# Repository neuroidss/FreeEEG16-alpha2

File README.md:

# FreeEEG16-alpha2

[https://neuroidss.github.io/NEURO-CULTIVATION/](https://neuroidss.github.io/NEURO-CULTIVATION/)

This project relies on a custom ultra-high-density EEG device, NOT a standard medical or consumer EEG headset.
- **Device Name:** FreeEEG16-alpha2
- **Form Factor:** 26mm diameter circular PCB.
- **Electrode Array:** 18 pogo pins tightly packed within the 26mm area.
  - 16 Active Positive Channels (+)
  - 1 Common Reference (-)
  - 1 Ground (GND)
- **Placement:** Works entirely locally, primarily targeted at the Pz (parietal) placement.
- **Key Capability:** NO distant electrodes are required. Reference and Ground are located in the same 26mm cluster as the active channels.
- **Performance:** When placed on Pz, the system provides a high-fidelity real-time loop. Users can observe immediate bio-reactive changes in procedural shaders, minimizing the cognitive load required to establish stable neurofeedback.

[Neuro_Test_Bench_PRO_16CH](https://neuroidss.github.io/FreeEEG16-alpha2/Neuro_Test_Bench/Neuro_Test_Bench_PRO_16CH.html)

[FreeEEG16-alpha_2_1_gerbers](https://github.com/neuroidss/FreeEEG16-alpha2/releases/tag/FreeEEG16-alpha_2_1_gerbers)

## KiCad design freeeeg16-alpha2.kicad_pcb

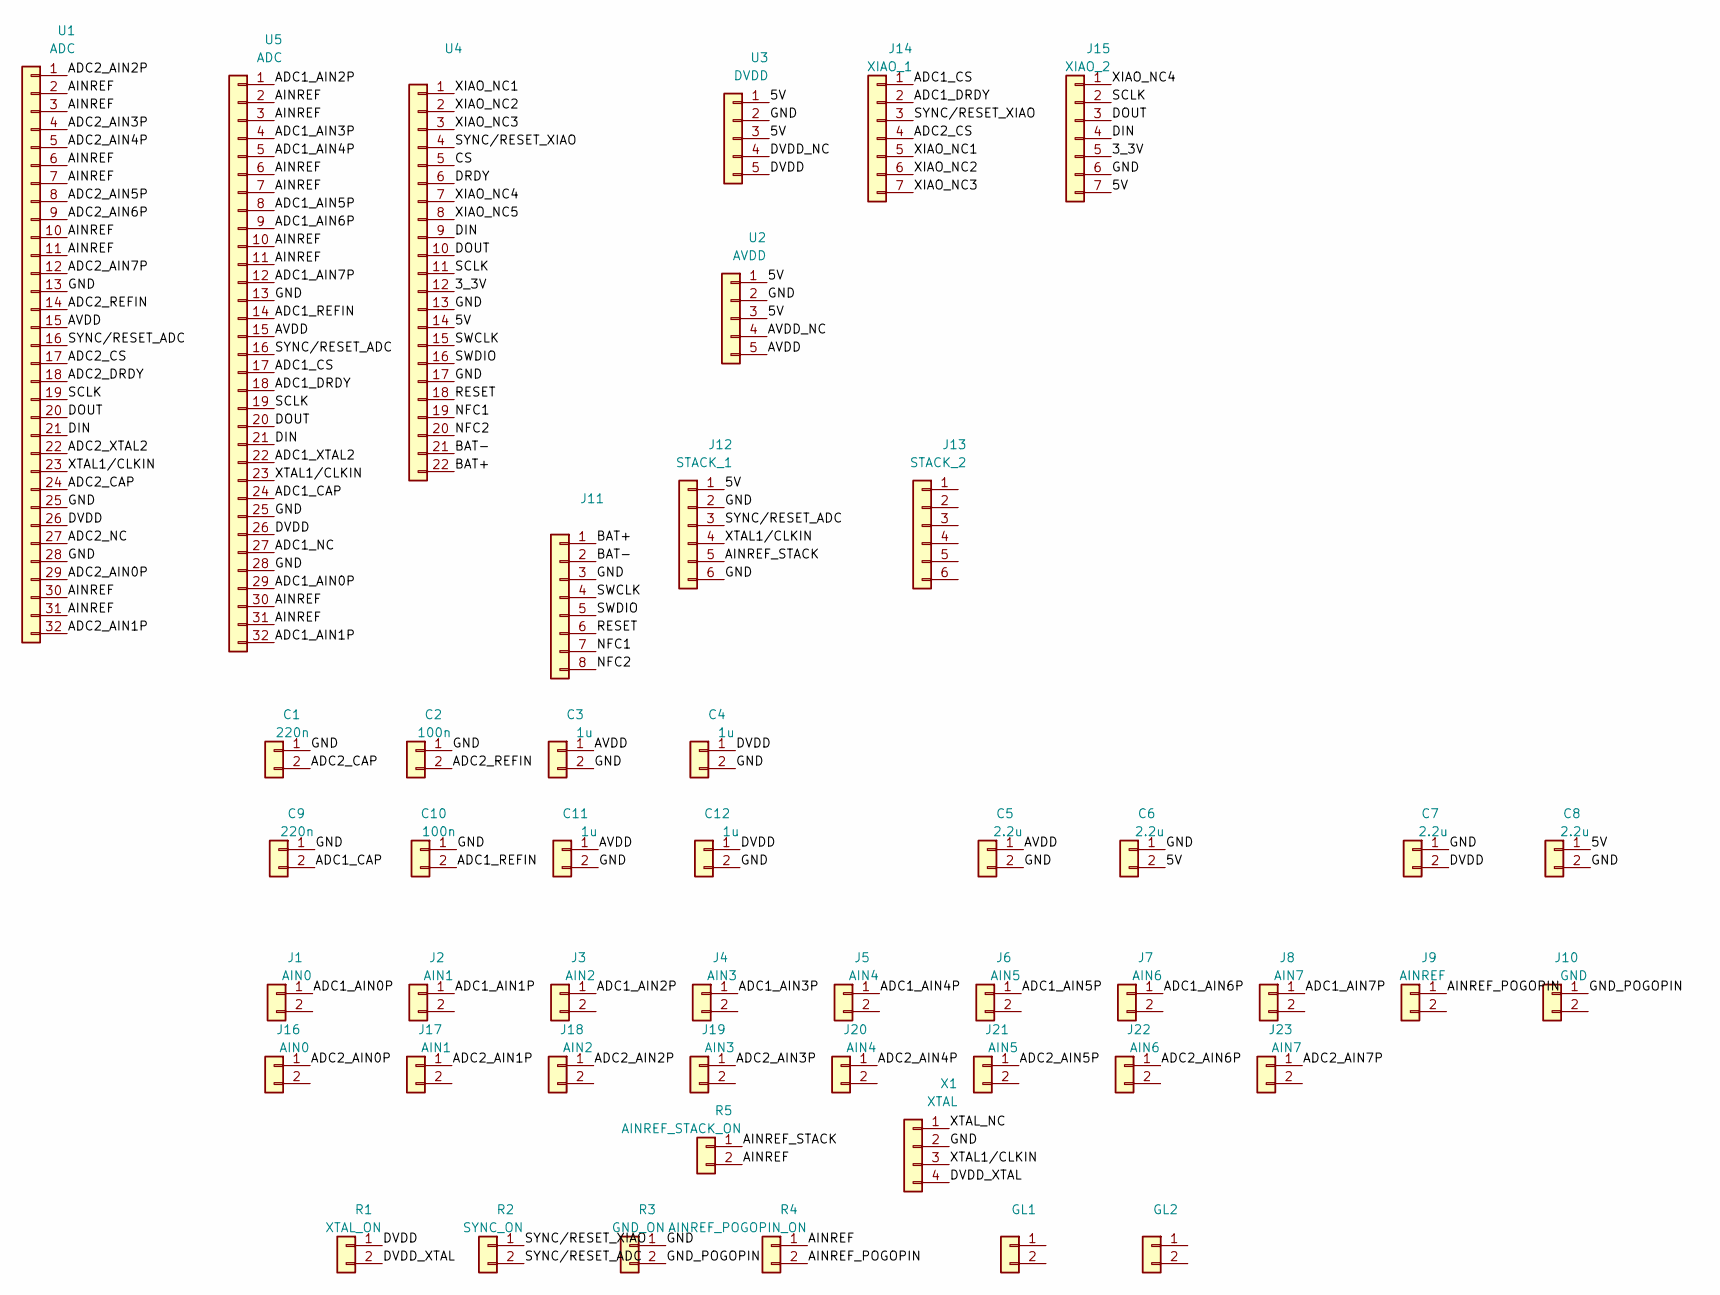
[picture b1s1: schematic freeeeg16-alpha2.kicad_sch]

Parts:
C1, C9: 220n; C_0402_1005Metric; MPN CC0402KRX5R5BB224
C2, C10: 100n; C_0402_1005Metric; MPN CL05B104KO5NNNC
C3, C4, C11, C12: 1u; C_0402_1005Metric; MPN CL05A105KO5NNNC
C5, C6, C7, C8: 2.2u; C_0603_1608Metric; MPN GRM188R71A225KE15D
GL1: FreeEEG8-alpha-title_5mm_SilkScreen
GL2: NeuroIDSS-url_5mm_SilkScreen
J1, J16: AIN0; pogo_pin_d5x10mm_smd; MPN pogo-pin-d5x10mm-smd
J2, J17: AIN1; pogo_pin_d5x10mm_smd; MPN pogo-pin-d5x10mm-smd
J3, J18: AIN2; pogo_pin_d5x10mm_smd; MPN pogo-pin-d5x10mm-smd
J4, J19: AIN3; pogo_pin_d5x10mm_smd; MPN pogo-pin-d5x10mm-smd
J5, J20: AIN4; pogo_pin_d5x10mm_smd; MPN pogo-pin-d5x10mm-smd
J6, J21: AIN5; pogo_pin_d5x10mm_smd; MPN pogo-pin-d5x10mm-smd
J7, J22: AIN6; pogo_pin_d5x10mm_smd; MPN pogo-pin-d5x10mm-smd
J8, J23: AIN7; pogo_pin_d5x10mm_smd; MPN pogo-pin-d5x10mm-smd
J9: AINREF; pogo_pin_d5x10mm_smd; MPN pogo-pin-d5x10mm-smd
J10: GND; pogo_pin_d5x10mm_smd; MPN pogo-pin-d5x10mm-smd
J11: Molex_PicoBlade_53398-0871_1x08-1MP_P1.25mm_Vertical_DNP
J12: STACK_1; Molex_PicoBlade_53398-0671_1x06-1MP_P1.25mm_Vertical_DNP; MPN 53398-0671
J13: STACK_2; Molex_PicoBlade_53398-0671_1x06-1MP_P1.25mm_Vertical_DNP; MPN 53398-0671
J14: XIAO_1; PinHeader_1x07_P2.54mm_Vertical_SMD_Pin1Right; MPN TSM-107-01-L-SV
J15: XIAO_2; PinHeader_1x07_P2.54mm_Vertical_SMD_Pin1Right; MPN TSM-107-01-L-SV
R1: XTAL_ON; R_0402_1005Metric; MPN RC0402JR-070RL
R2: SYNC_ON; R_0402_1005Metric; MPN RC0402JR-070RL
R3: GND_ON; R_0402_1005Metric; MPN RC0402JR-070RL
R4: AINREF_POGOPIN_ON; R_0402_1005Metric; MPN RC0402JR-070RL
R5: AINREF_STACK_ON; R_0402_1005Metric; MPN DNP
U1, U5: ADC; LQFP-32_5x5mm_P0.5mm; MPN ADS131M08IPBSR
U2: AVDD; SOT-23-5; MPN LP5907QMFX-3.3Q1
U3: DVDD; SOT-23-5; MPN LP5907QMFX-3.3Q1
U4: XIAO-nRF52840-Sense-14P-2.54-21X17.8MM
X1: XTAL; Oscillator_SMD_EuroQuartz_XO32-4Pin_3.2x2.5mm_HandSoldering; MPN ECS-2520MVLC-081.92-CN-TR

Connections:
/3_3V: J15.5, U4.12
/5V: C6.2, C8.1, J12.1, J15.7, U2.1, U2.3, U3.1, U3.3, U4.14
/ADC1_AIN0P: J1.1, U5.29
/ADC1_AIN1P: J2.1, U5.32
/ADC1_AIN2P: J3.1, U5.1
/ADC1_AIN3P: J4.1, U5.4
/ADC1_AIN4P: J5.1, U5.5
/ADC1_AIN5P: J6.1, U5.8
/ADC1_AIN6P: J7.1, U5.9
/ADC1_AIN7P: J8.1, U5.12
/ADC1_CAP: C9.2, U5.24
/ADC1_CS: J14.1, U5.17
/ADC1_DRDY: J14.2, U5.18
/ADC1_NC: U5.27
/ADC1_REFIN: C10.2, U5.14
/ADC1_XTAL2: U5.22
/ADC2_AIN0P: J16.1, U1.29
/ADC2_AIN1P: J17.1, U1.32
/ADC2_AIN2P: J18.1, U1.1
/ADC2_AIN3P: J19.1, U1.4
/ADC2_AIN4P: J20.1, U1.5
/ADC2_AIN5P: J21.1, U1.8
/ADC2_AIN6P: J22.1, U1.9
/ADC2_AIN7P: J23.1, U1.12
/ADC2_CAP: C1.2, U1.24
/ADC2_CS: J14.4, U1.17
/ADC2_DRDY: U1.18
/ADC2_NC: U1.27
/ADC2_REFIN: C2.2, U1.14
/ADC2_XTAL2: U1.22
/AINREF: R4.1, R5.2, U1.2, U1.3, U1.6, U1.7, U1.10, U1.11, U1.30, U1.31, U5.2, U5.3, U5.6, U5.7, U5.10, U5.11, U5.30, U5.31
/AINREF_POGOPIN: J9.1, R4.2
/AINREF_STACK: J12.5, R5.1
/AVDD: C3.1, C5.1, C11.1, U1.15, U2.5, U5.15
/AVDD_NC: U2.4
/DIN: J15.4, U1.21, U4.9, U5.21
/DOUT: J15.3, U1.20, U4.10, U5.20
/DVDD: C4.1, C7.2, C12.1, R1.1, U1.26, U3.5, U5.26
/DVDD_NC: U3.4
/DVDD_XTAL: R1.2, X1.4
/GND: C1.1, C2.1, C3.2, C4.2, C5.2, C6.1, C7.1, C8.2, C9.1, C10.1, C11.2, C12.2, J11.3, J12.2, J12.6, J15.6, R3.1, U1.13, U1.25, U1.28, U2.2, U3.2, U4.13, U4.17, U5.13, U5.25, U5.28, X1.2
/GND_POGOPIN: J10.1, R3.2
/SCLK: J15.2, U1.19, U4.11, U5.19
/SYNC/RESET_ADC: J12.3, R2.2, U1.16, U5.16
/SYNC/RESET_XIAO: J14.3, R2.1, U4.4
/XIAO_NC1: J14.5, U4.1
/XIAO_NC2: J14.6, U4.2
/XIAO_NC3: J14.7, U4.3
/XIAO_NC4: J15.1, U4.7
/XTAL1/CLKIN: J12.4, U1.23, U5.23, X1.3
/XTAL_NC: X1.1
unnamed: J11.1, U4.22
unnamed: J11.2, U4.21
unnamed: J11.4, U4.15
unnamed: J11.5, U4.16
unnamed: J11.6, U4.18
unnamed: J11.7, U4.19
unnamed: J11.8, U4.20

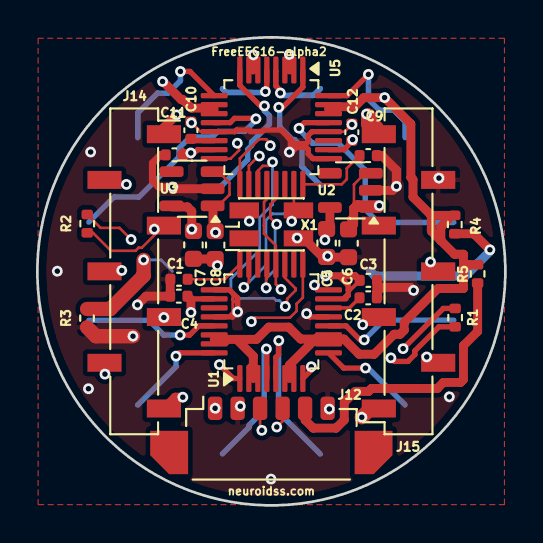
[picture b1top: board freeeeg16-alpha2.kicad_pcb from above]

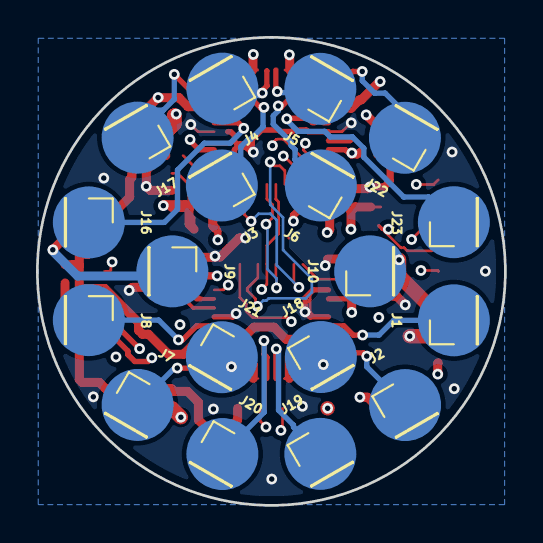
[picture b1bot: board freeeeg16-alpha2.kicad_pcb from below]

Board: 4 copper layers, 26.0 x 26.0 mm, 45 parts (18 on the bottom side), 38 nets.
